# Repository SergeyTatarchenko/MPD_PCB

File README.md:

# MPD_PCB
schematics and pcb layouts for motor protection device

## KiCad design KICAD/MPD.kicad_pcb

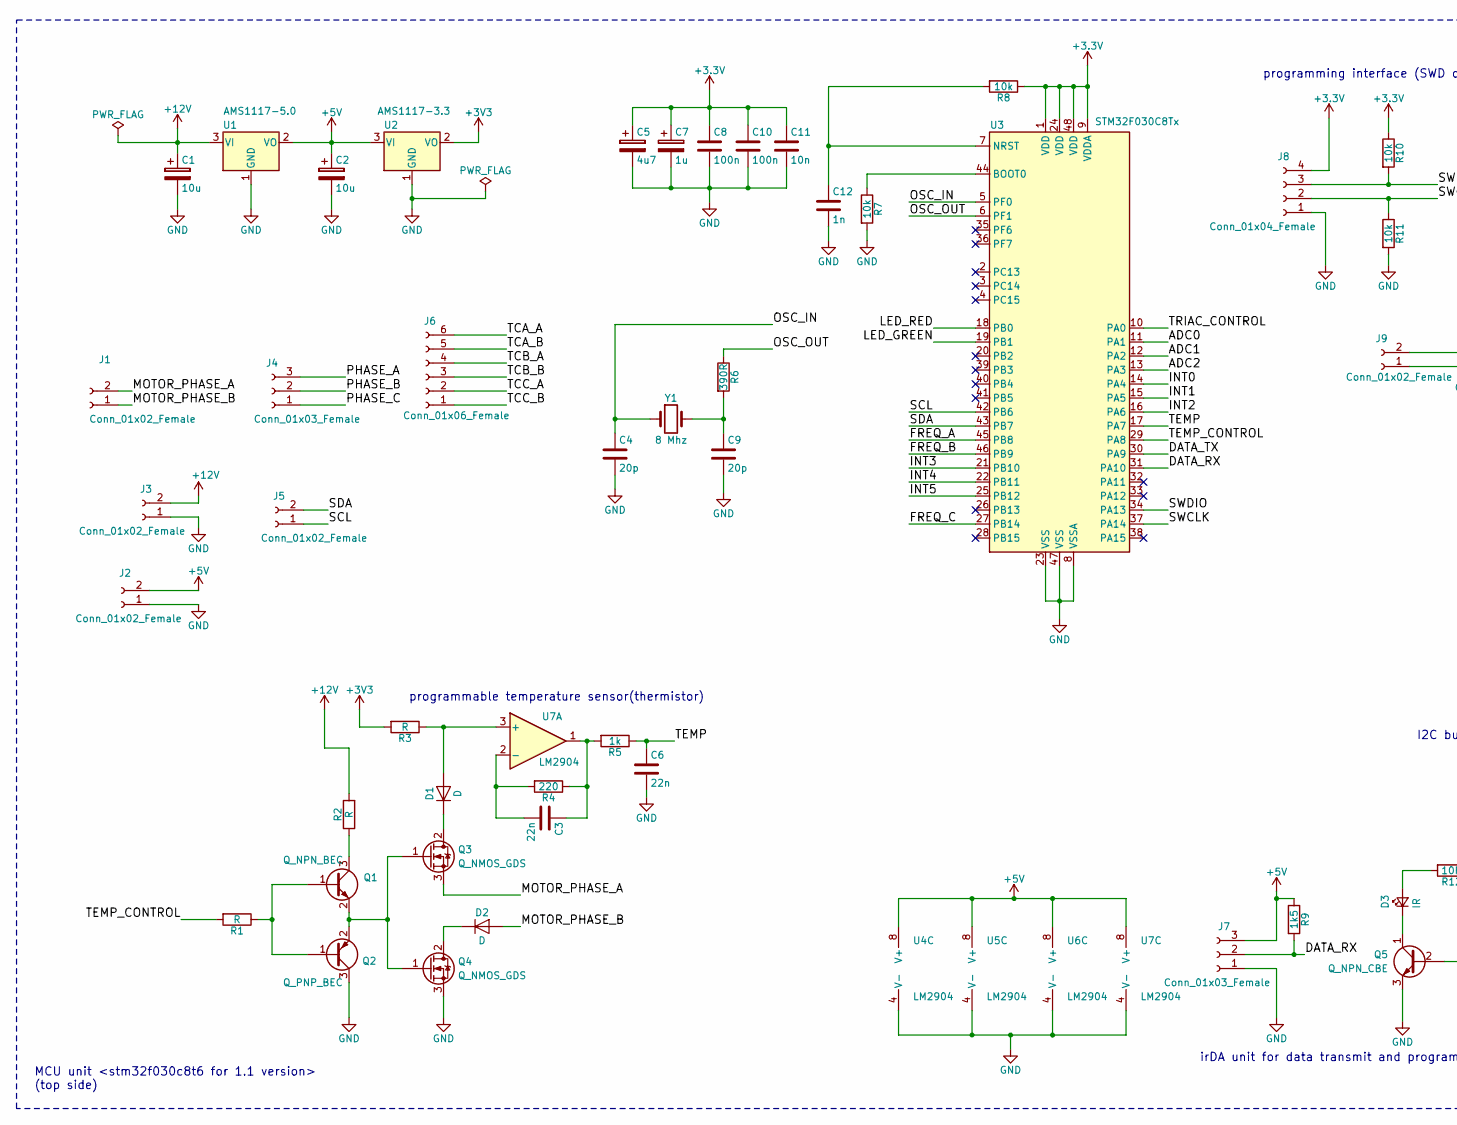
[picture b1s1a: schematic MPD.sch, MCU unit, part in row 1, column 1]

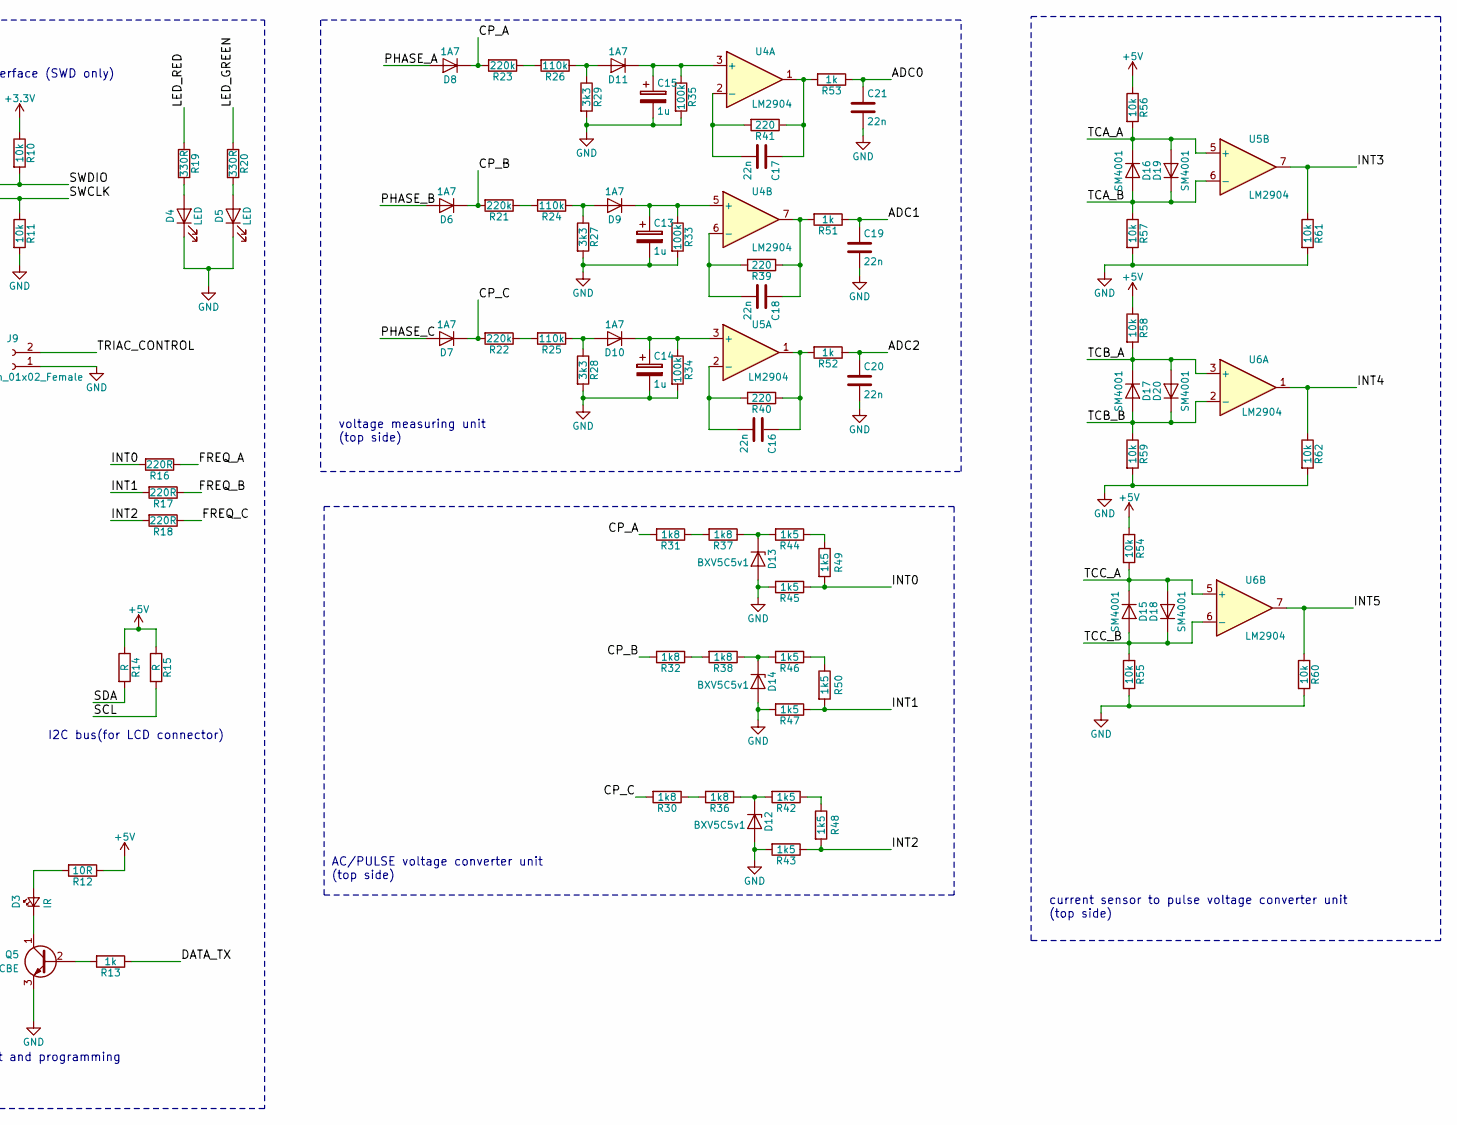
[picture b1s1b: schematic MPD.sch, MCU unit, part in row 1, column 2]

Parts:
C1, C2: 10u; CP_Elec_6.3x5.4
C3, C6, C16, C17, C18, C19, C20, C21: 22n; C_1206_3216Metric_Pad1.42x1.75mm_HandSolder
C4, C9: 20p; C_1206_3216Metric_Pad1.42x1.75mm_HandSolder
C5: 4u7; CP_Elec_4x5.4
C7, C13, C14, C15: 1u; CP_Elec_4x5.4
C8, C10: 100n; C_1206_3216Metric_Pad1.42x1.75mm_HandSolder
C11: 10n; C_1206_3216Metric_Pad1.42x1.75mm_HandSolder
C12: 1n; C_1206_3216Metric_Pad1.42x1.75mm_HandSolder
D1, D2: D; D_SMB
D3: IR; LED_D5.0mm
D4, D5: LED; LED_0805_2012Metric
D6, D7, D8: 1A7; D_DO-41_SOD81_P2.54mm_Vertical_AnodeUp
D9, D10, D11: 1A7; D_SMA
D12, D13, D14: BXV5C5v1; D_DO-41_SOD81_P2.54mm_Vertical_AnodeUp
D15, D16, D17, D18, D19, D20: SM4001; D_SMA
J1, J2, J3, J5, J9: Conn_01x02_Female; PinHeader_1x02_P2.54mm_Vertical
J4, J7: Conn_01x03_Female; PinHeader_1x03_P2.54mm_Vertical
J6: Conn_01x06_Female; PinHeader_1x06_P2.54mm_Vertical
J8: Conn_01x04_Female; PinHeader_1x04_P2.54mm_Vertical
Q1: Q_NPN_BEC; SOT-23
Q2: Q_PNP_BEC; SOT-23
Q3, Q4: Q_NMOS_GDS; SOT-223-3_TabPin2
Q5: Q_NPN_CBE; SOT-23
R1, R2, R3, R14, R15: R; R_1206_3216Metric_Pad1.42x1.75mm_HandSolder
R4, R39, R40, R41: 220; R_1206_3216Metric_Pad1.42x1.75mm_HandSolder
R5, R13, R51, R52, R53: 1k; R_1206_3216Metric_Pad1.42x1.75mm_HandSolder
R6: 390R; R_1206_3216Metric_Pad1.42x1.75mm_HandSolder
R7, R8, R10, R11, R54, R55, R56, R57, R58, R59, R60, R61, R62: 10k; R_1206_3216Metric_Pad1.42x1.75mm_HandSolder
R9, R42, R43, R44, R45, R46, R47, R48, R49, R50: 1k5; R_1206_3216Metric_Pad1.42x1.75mm_HandSolder
R12: 10R; R_1206_3216Metric_Pad1.42x1.75mm_HandSolder
R16, R17, R18: 220R; R_1206_3216Metric_Pad1.42x1.75mm_HandSolder
R19, R20: 330R; R_1206_3216Metric_Pad1.42x1.75mm_HandSolder
R21, R22, R23: 220k; R_1206_3216Metric_Pad1.42x1.75mm_HandSolder
R24, R25, R26: 110k; R_1206_3216Metric_Pad1.42x1.75mm_HandSolder
R27, R28, R29: 3k3; R_1206_3216Metric_Pad1.42x1.75mm_HandSolder
R30, R31, R32, R36, R37, R38: 1k8; R_1206_3216Metric_Pad1.42x1.75mm_HandSolder
R33, R34, R35: 100k; R_1206_3216Metric_Pad1.42x1.75mm_HandSolder
U1: AMS1117-5.0; SOT-223-3_TabPin2
U2: AMS1117-3.3; SOT-223-3_TabPin2
U3: STM32F030C8Tx; LQFP-48_7x7mm_P0.5mm
U4, U5, U6, U7: LM2904; Zetex_SM8
Y1: 8 Mhz; Crystal_SMD_HC49-SD

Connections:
+5V: C2.1, J2.2, J7.3, R9.1, R12.1, R14.1, R15.1, R54.1, R56.1, R58.1, U1.2 (VO), U2.3 (VI), U4.8 (V+), U5.8 (V+), U6.8 (V+), U7.8 (V+)
+12V: C1.1, J3.2, R2.2, U1.3 (VI)
/ADC0: C21.1, R53.1, U3.11 (PA1)
/ADC1: C19.1, R51.1, U3.12 (PA2)
/ADC2: C20.1, R52.1, U3.13 (PA3)
/CP_A: D8.1 (K), R23.2, R31.2
/CP_B: D6.1 (K), R21.2, R32.2
/CP_C: D7.1 (K), R22.2, R30.2
/DATA_RX: J7.2, R9.2, U3.31 (PA10)
/DATA_TX: R13.1, U3.30 (PA9)
/FREQ_A: R16.1, U3.45 (PB8)
/FREQ_B: R17.1, U3.46 (PB9)
/FREQ_C: R18.1, U3.27 (PB14)
/INT0: R16.2, R45.1, R49.2, U3.14 (PA4)
/INT1: R17.2, R47.1, R50.2, U3.15 (PA5)
/INT2: R18.2, R43.1, R48.2, U3.16 (PA6)
/INT3: R61.1, U3.21 (PB10), U5.7
/INT4: R62.1, U3.22 (PB11), U6.1
/INT5: R60.1, U3.25 (PB12), U6.7
/LED_GREEN: R20.1, U3.19 (PB1)
/LED_RED: R19.1, U3.18 (PB0)
/MOTOR_PHASE_A: J1.2, Q3.3 (S)
/MOTOR_PHASE_B: D2.2 (A), J1.1
/OSC_IN: C4.1, U3.5 (PF0), Y1.1
/OSC_OUT: R6.1, U3.6 (PF1)
/PHASE_A: D8.2 (A), J4.3
/PHASE_B: D6.2 (A), J4.2
/PHASE_C: D7.2 (A), J4.1
/SCL: J5.1, R15.2, U3.42 (PB6)
/SDA: J5.2, R14.2, U3.43 (PB7)
/SWCLK: J8.2, R11.1, U3.37 (PA14)
/SWDIO: J8.3, R10.2, U3.34 (PA13)
/TCA_A: D16.1 (K), D19.2 (A), J6.6, R56.2, U5.5 (+)
/TCA_B: D16.2 (A), D19.1 (K), J6.5, R57.1, U5.6 (-)
/TCB_A: D17.1 (K), D20.2 (A), J6.4, R58.2, U6.3 (+)
/TCB_B: D17.2 (A), D20.1 (K), J6.3, R59.1, U6.2 (-)
/TCC_A: D15.1 (K), D18.2 (A), J6.2, R54.2, U6.5 (+)
/TCC_B: D15.2 (A), D18.1 (K), J6.1, R55.1, U6.6 (-)
/TEMP: C6.1, R5.1, U3.17 (PA7)
/TEMP_CONTROL: R1.2, U3.29 (PA8)
/TRIAC_CONTROL: J9.2, U3.10 (PA0)
GND: C1.2, C2.2, C4.2, C5.2, C6.2, C7.2, C8.2, C9.2, C10.2, C11.2, C12.2, C13.2, C14.2, C15.2, C19.2, C20.2, C21.2, D4.1 (K), D5.1 (K), D12.2 (A), D13.2 (A), D14.2 (A), J2.1, J3.1, J7.1, J8.1, J9.1, Q2.3 (C), Q4.3 (S), Q5.3 (E), R7.2, R11.2, R27.2, R28.2, R29.2, R33.2, R34.2, R35.2, R43.2, R45.2, R47.2, R55.2, R57.2, R59.2, R60.2, R61.2, R62.2, U1.1 (GND), U2.1 (GND), U3.8 (VSSA), U3.23 (VSS), U3.47 (VSS), U4.4 (V-), U5.4 (V-), U6.4 (V-), U7.4 (V-)
unnamed: C3.1, R4.1, R5.2, U7.1
unnamed: C3.2, R4.2, U7.2 (-)
unnamed: C9.1, R6.2, Y1.2
unnamed: C12.1, R8.2, U3.7 (NRST)
unnamed: C13.1, D9.1 (K), R33.1, U4.5 (+)
unnamed: C14.1, D10.1 (K), R34.1, U5.3 (+)
unnamed: C15.1, D11.1 (K), R35.1, U4.3 (+)
unnamed: C16.1, R40.1, R52.2, U5.1
unnamed: C16.2, R40.2, U5.2 (-)
unnamed: C17.1, R41.1, R53.2, U4.1
unnamed: C17.2, R41.2, U4.2 (-)
unnamed: C18.1, R39.1, R51.2, U4.7
unnamed: C18.2, R39.2, U4.6 (-)
unnamed: D1.1 (K), Q3.2 (D)
unnamed: D1.2 (A), R3.1, U7.3 (+)
unnamed: D2.1 (K), Q4.2 (D)
unnamed: D3.1 (K), Q5.1 (C)
unnamed: D3.2 (A), R12.2
unnamed: D4.2 (A), R19.2
unnamed: D5.2 (A), R20.2
unnamed: D9.2 (A), R24.1, R27.1
unnamed: D10.2 (A), R25.1, R28.1
unnamed: D11.2 (A), R26.1, R29.1
unnamed: D12.1 (K), R36.1, R42.2
unnamed: D13.1 (K), R37.1, R44.2
unnamed: D14.1 (K), R38.1, R46.2
unnamed: Q1.1 (B), Q2.1 (B), R1.1
unnamed: Q1.2 (E), Q2.2 (E), Q3.1 (G), Q4.1 (G)
unnamed: Q1.3 (C), R2.1
unnamed: Q5.2 (B), R13.2
unnamed: R7.1, U3.44 (BOOT0)
unnamed: R21.1, R24.2
unnamed: R22.1, R25.2
unnamed: R23.1, R26.2
unnamed: R30.1, R36.2
unnamed: R31.1, R37.2
unnamed: R32.1, R38.2
unnamed: R42.1, R48.1
unnamed: R44.1, R49.1
unnamed: R46.1, R50.1

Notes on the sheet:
voltage measuring unit (top side)
AC/PULSE voltage converter unit (top side)
current sensor to pulse voltage converter unit (top side)
MCU unit <stm32f030c8t6 for 1.1 version> (top side)
programming interface (SWD only)
programmable temperature sensor(thermistor)
irDA unit for data transmit and programming
I2C bus(for LCD connector)

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
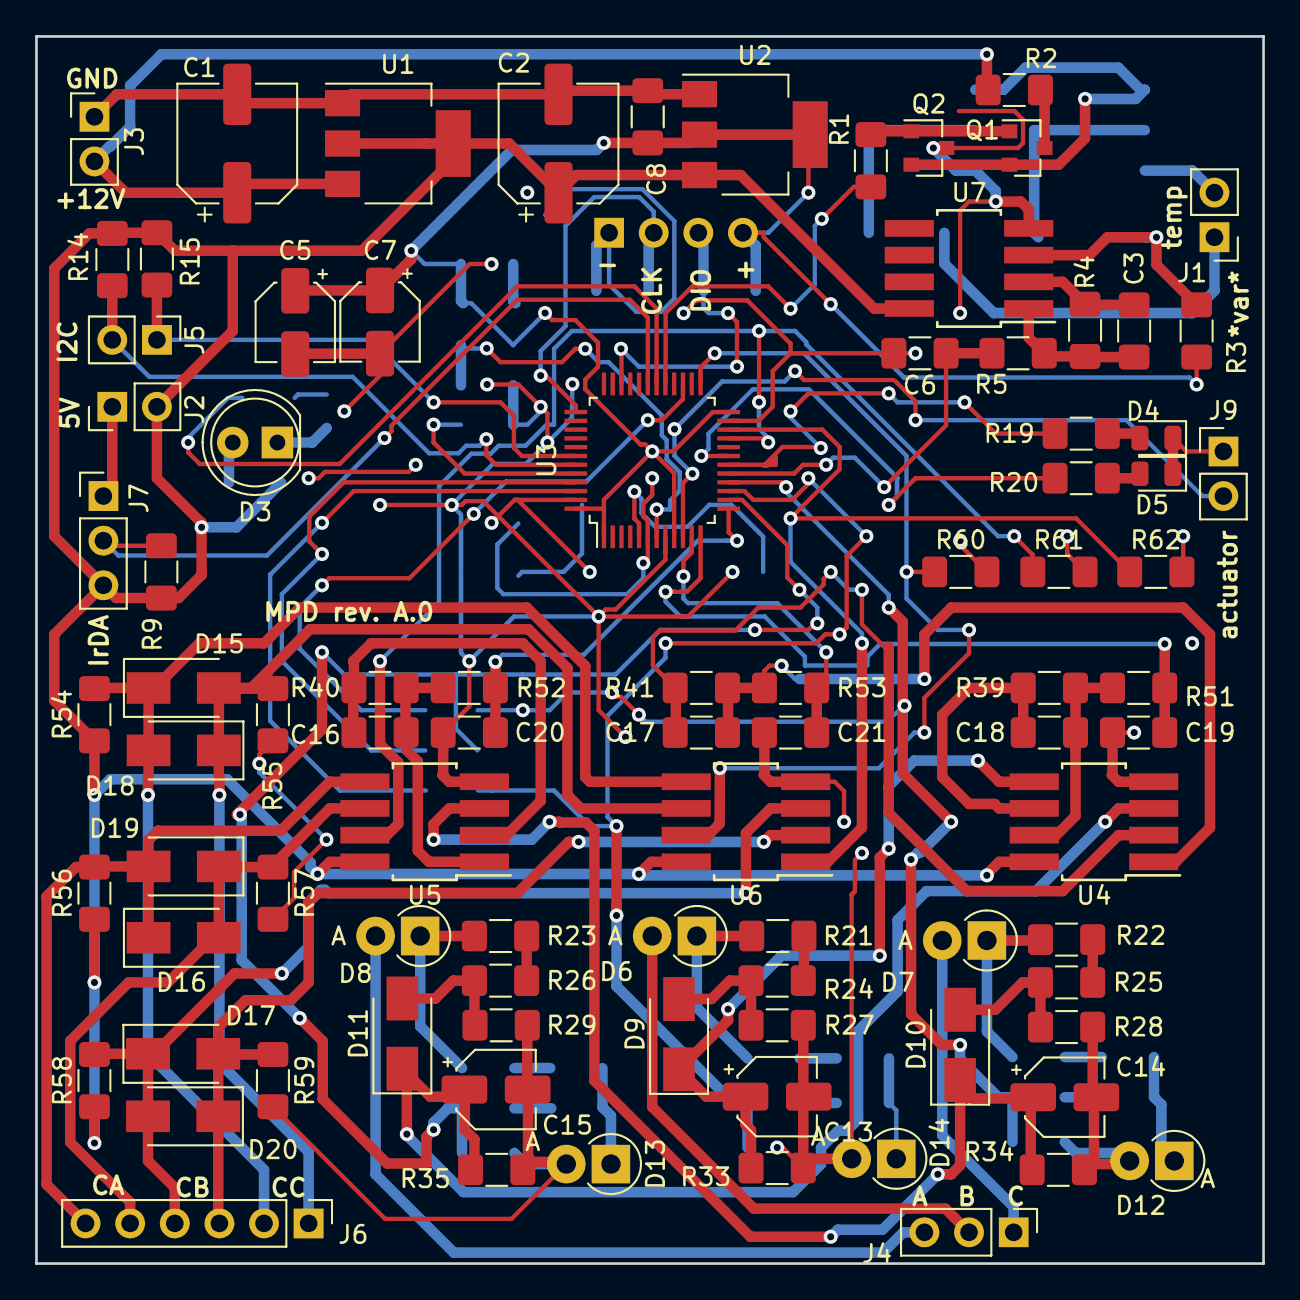
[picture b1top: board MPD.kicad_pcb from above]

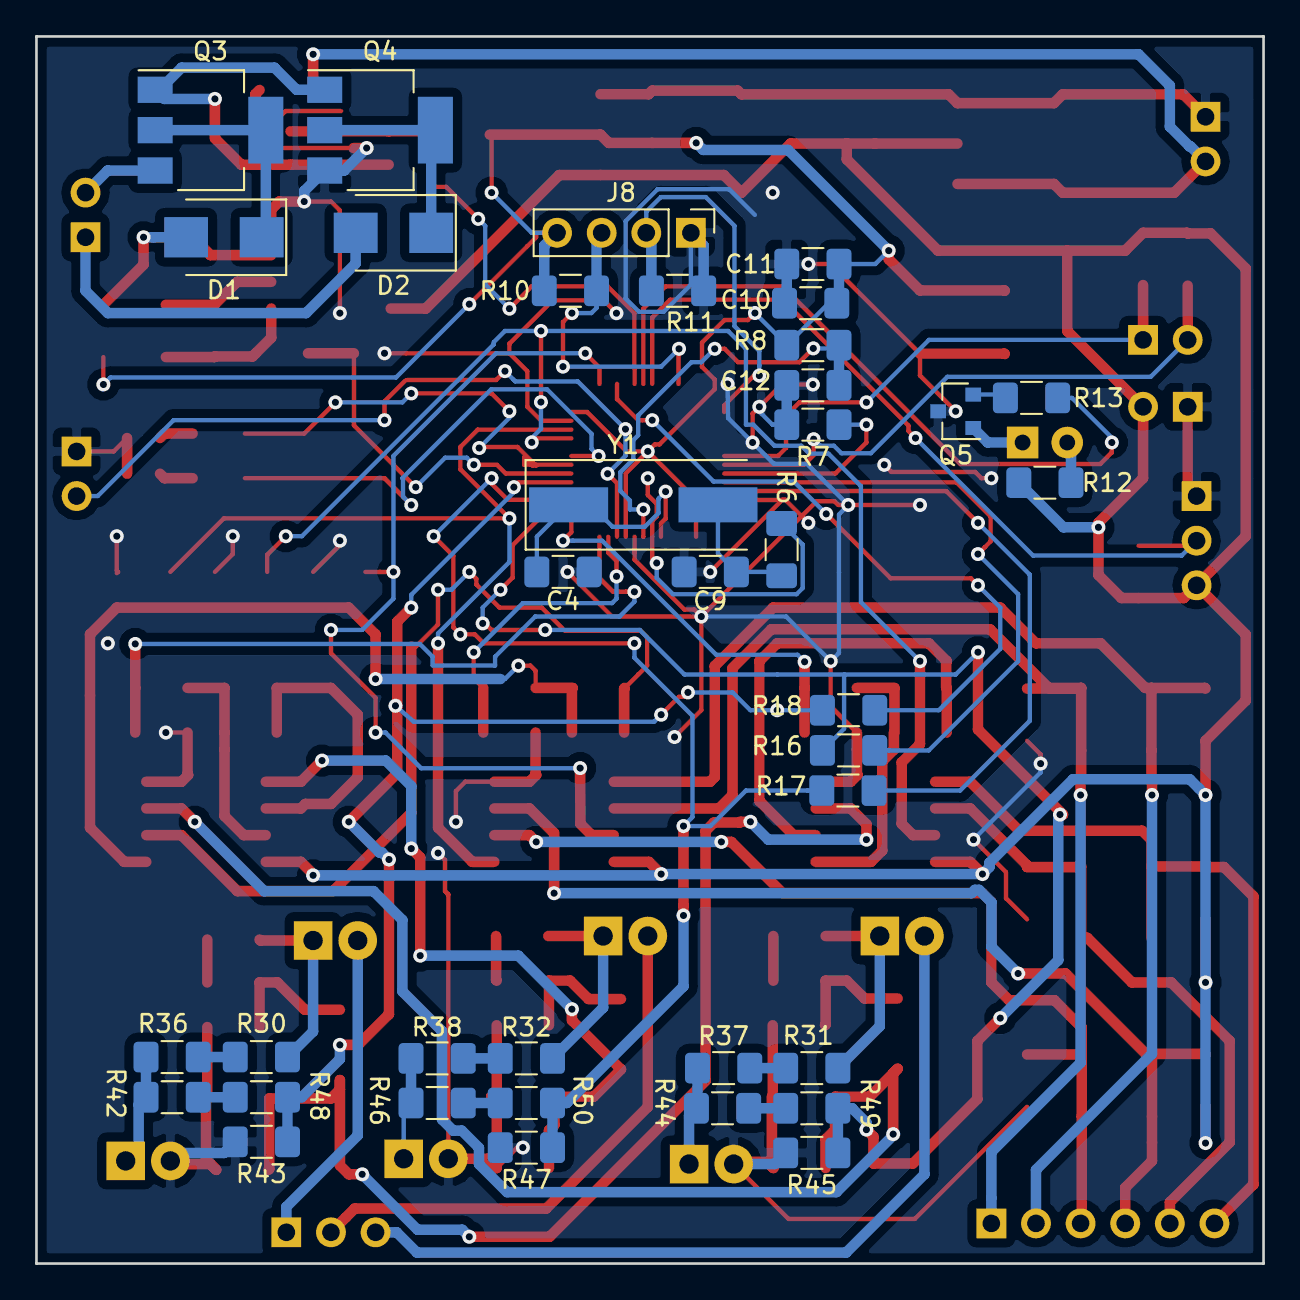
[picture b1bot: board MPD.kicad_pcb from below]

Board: 2 copper layers, 69.8 x 69.9 mm, 125 parts (37 on the bottom side), 83 nets.

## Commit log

2019-09-08 Init
2019-09-14 working on schematic (version 1.1)
2019-09-15 update schematic
2019-09-22 finished schematic for alfa version
2019-09-22 add pdf
2019-10-13 fix mcu unit
2019-10-20 KiCAD version 5.0 fix schematics
2019-10-28 -pcb finished
2019-10-30 MPD rev.A0 released
